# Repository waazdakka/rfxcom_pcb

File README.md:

# RFXCom PCB

This PCB aims to replace wires in a RFXCom project using:
* an Arduino Mega 2560
* a RXB6 Super Heterodyne receiver
* a XD-FST FS1000A emitter

(See https://opendomotech.com/fabriquer-rflink-alternative-diy-du-rfxcom/)

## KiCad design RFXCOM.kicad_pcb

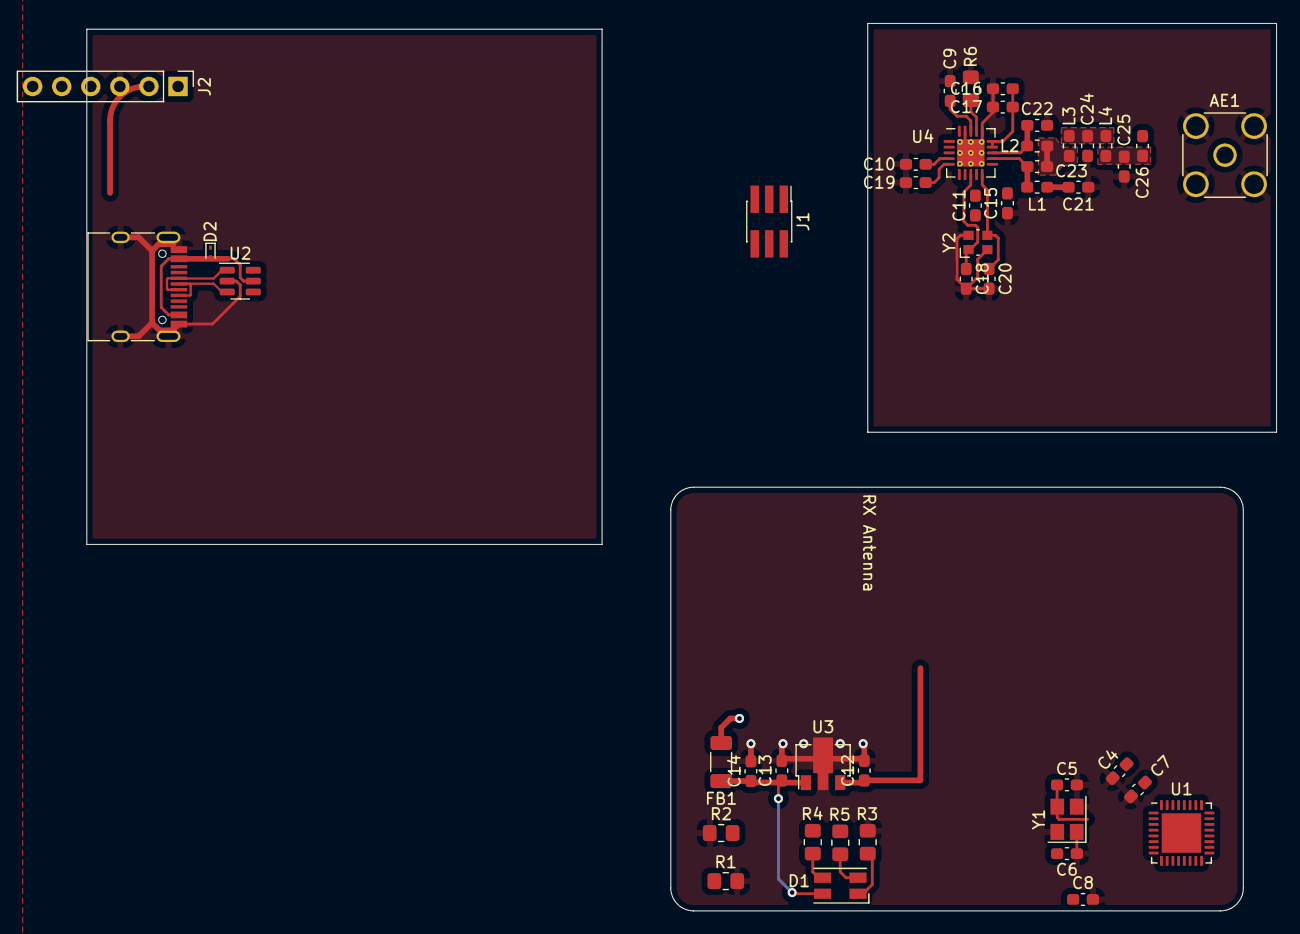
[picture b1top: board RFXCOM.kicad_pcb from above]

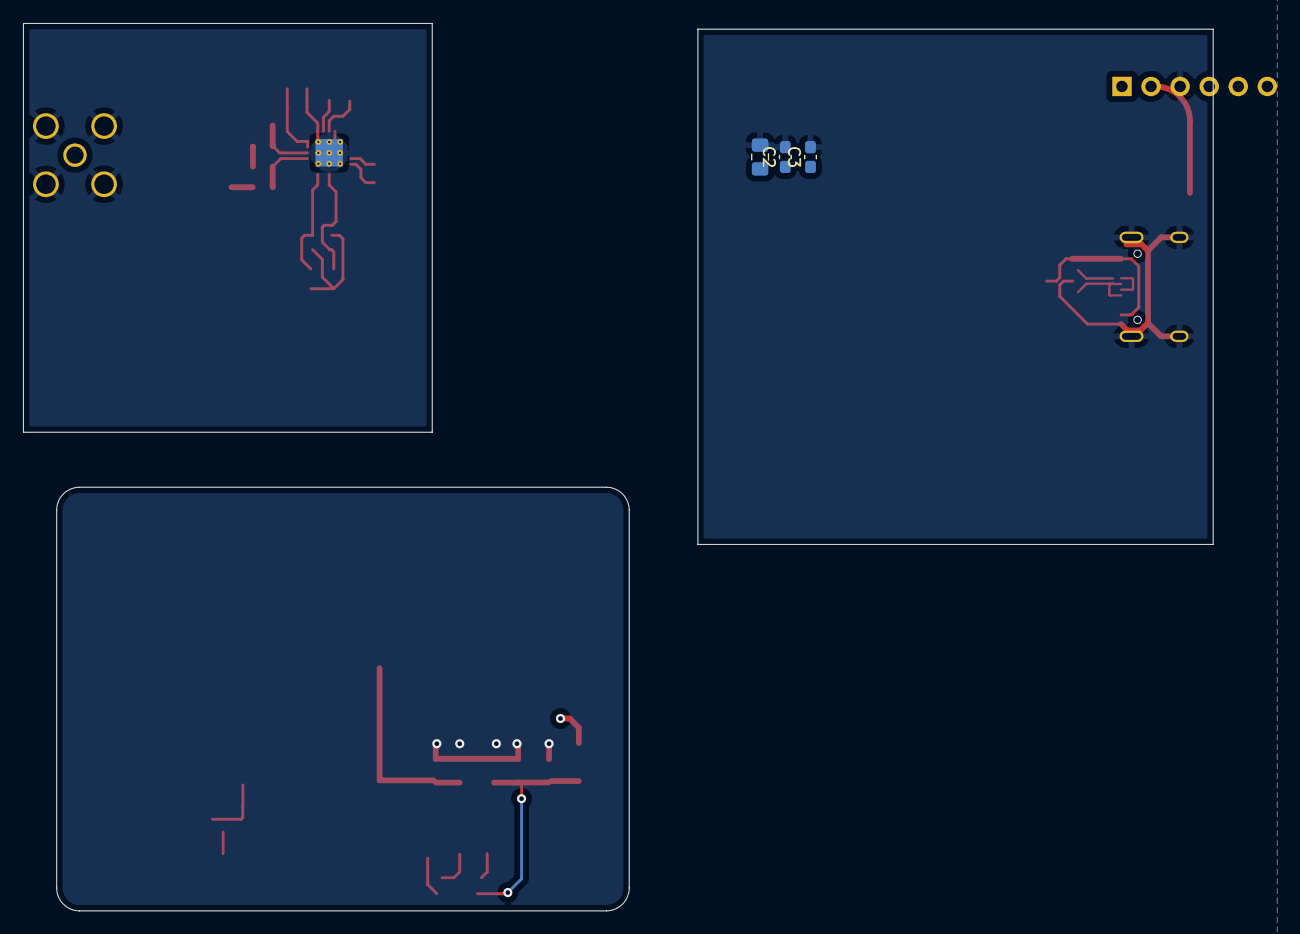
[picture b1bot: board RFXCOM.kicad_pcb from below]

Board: 2 copper layers, 103.9 x 77.5 mm, 49 parts (3 on the bottom side), 32 nets.

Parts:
AE1: Antenna_Shield; SMA_Amphenol_132134_Vertical
C1: 4u7; C_0805_2012Metric_Pad1.18x1.45mm_HandSolder
C2, C3, C7, C9, C10, C11, C15, C16, C17, C19: 100n; C_0603_1608Metric_Pad1.08x0.95mm_HandSolder
C4, C5: 10p; C_0603_1608Metric_Pad1.08x0.95mm_HandSolder
C6, C14: 1u; C_0603_1608Metric_Pad1.08x0.95mm_HandSolder
C8: 10n; C_0603_1608Metric_Pad1.08x0.95mm_HandSolder
C12: 2u; C_0603_1608Metric_Pad1.08x0.95mm_HandSolder
C13: 3u3; C_0603_1608Metric_Pad1.08x0.95mm_HandSolder
C18, C20: 22pF; C_0603_1608Metric_Pad1.08x0.95mm_HandSolder
C21: 220pF; C_0603_1608Metric_Pad1.08x0.95mm_HandSolder
C22, C23: 3.9pF; C_0603_1608Metric_Pad1.08x0.95mm_HandSolder
C24: 8.2pF; C_0603_1608Metric_Pad1.08x0.95mm_HandSolder
C25: 5.6pf; C_0603_1608Metric_Pad1.08x0.95mm_HandSolder
C26: 0.9pF; C_0603_1608Metric_Pad1.08x0.95mm_HandSolder
D1: LED_AGRB; LED_RGB_Wuerth-PLCC4_3.2x2.8mm_150141M173100
D2: ESD9X5.0ST5G; D_SOD-923
FB1: 120R; L_1206_3216Metric_Pad1.22x1.90mm_HandSolder
J1: SWD; PinHeader_2x03_P1.27mm_Vertical_SMD
J2: SWD_Connector; PinHeader_1x06_P2.54mm_Vertical
J6: USB_C_Receptacle_USB2.0; USB_C_Receptacle_HRO_TYPE-C-31-M-12
L1, L2, L4: 27nH; L_0603_1608Metric_Pad1.05x0.95mm_HandSolder
L3: 22nH; L_0603_1608Metric_Pad1.05x0.95mm_HandSolder
R1, R2: 5k1; R_0805_2012Metric_Pad1.20x1.40mm_HandSolder
R3: 130; R_0805_2012Metric_Pad1.20x1.40mm_HandSolder
R4, R5: 30; R_0805_2012Metric_Pad1.20x1.40mm_HandSolder
R6: 56k; R_0805_2012Metric_Pad1.20x1.40mm_HandSolder
U1: STM32L412KBTx; QFN-32-1EP_5x5mm_P0.5mm_EP3.45x3.45mm
U2: USBLC6-2SC6; SOT-23-6
U3: LD2981ABU33TR; SOT-89-3
U4: CC110L; Texas_S-PVQFN-N20_EP2.4x2.4mm_ThermalVias
Y1: 16M; Crystal_SMD_Abracon_ABM8G-4Pin_3.2x2.5mm
Y2: 26M; Crystal_SMD_Abracon_ABM10-4Pin_2.5x2.0mm

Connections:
+3.3V: C1.1, C2.1, C3.1, C9.2, C10.2, C11.2, C13.1, C14.1, C15.2, C16.2, C17.2, D1.1 (A), FB1.1, J1.1, U1.1 (VDD), U1.17 (VDD), U3.1 (VO), U4.4 (DVDD), U4.9 (AVDD), U4.11 (AVDD), U4.14 (AVDD), U4.15 (AVDD), U4.18 (DGUARD)
+3.3VA: C6.1, C8.1, FB1.2, U1.5 (VDDA)
+5V: C12.1, D2.2 (A2), J6.A4 (VBUS), J6.A9 (VBUS), J6.B4 (VBUS), J6.B9 (VBUS), U2.5 (VBUS), U3.3 (VI)
/MCU/SWCLK: J1.4, J2.2, U1.24 (PA14)
/MCU/SWDIO: J1.2, J2.4, U1.23 (PA13)
/MCU/SWO: J1.6, J2.6, U1.26 (PB3)
/MCU/USB_D+: U1.22 (PA12), U2.4 (I/O2)
/MCU/USB_D-: U1.21 (PA11), U2.6 (I/O1)
/MCU/~RST: C7.2, J1.3, J2.5, U1.4 (NRST)
/USB & Power Supply/USB_C_D+: J6.A6 (D+), J6.B6 (D+), U2.3 (I/O2)
/USB & Power Supply/USB_C_D-: J6.A7 (D-), J6.B7 (D-), U2.1 (I/O1)
GND: AE1.2 (Shield), C1.2, C2.2, C3.2, C4.1, C5.1, C6.2, C7.1, C8.2, C9.1, C10.1, C11.1, C12.2, C13.2, C14.2, C15.1, C16.1, C17.1, C18.2, C19.1, C20.2, C21.1, C22.2, C24.2, C25.2, D2.1 (A1), J1.5, J2.3, J6.A1 (GND), J6.A12 (GND), J6.B1 (GND), J6.B12 (GND), J6.S1 (SHIELD), R1.2, R2.1, R3.2, R6.2, U1.16 (VSS), U1.32 (VSS), U2.2 (GND), U3.2 (GND), U4.16 (GND), U4.19 (GND), U4.21 (PAD), Y1.2, Y1.4, Y2.2, Y2.4
unnamed: C4.2, U1.2 (PC14), Y1.3
unnamed: C5.2, U1.3 (PC15), Y1.1
unnamed: C19.2, U4.5 (DCOUPL)
unnamed: C21.2, L1.2
unnamed: C22.1, L2.2, U4.13 (RF_N)
unnamed: C23.1, L1.1, U4.12 (RF_P)
unnamed: C23.2, L2.1, L3.2
unnamed: C25.1, C26.1, L4.1
unnamed: AE1.1 (A), C26.2
unnamed: D1.2 (GK), R4.1
unnamed: D1.3 (RK), R3.1
unnamed: D1.4 (BK), R5.1
unnamed: J6.A5 (CC1), R1.1
unnamed: J6.B5 (CC2), R2.2
unnamed: C24.1, L3.1, L4.2
unnamed: R4.2, U1.29 (PB6)
unnamed: R5.2, U1.30 (PB7)
unnamed: R6.1, U4.17 (RBIAS)
unnamed: C18.1, U4.8 (XOSC_Q1), Y2.1
unnamed: C20.1, U4.10 (XOSC_Q2), Y2.3

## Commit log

2022-02-03 Add Kicad files
2022-02-03 Rework the schematics a bit with labels. Add a RXB6 footprint. Also add a .gitignore
2022-02-03 Remove local prl file
2022-10-14 New pcb on arduino mega pro, smoothed tracks, 2 antennas
2022-10-14 Fix labels on pcb, add screenshot
2022-10-14 Add readme
2022-11-07 Add XKFST component footprint
2022-11-11 Use correct footprint for TX
2022-11-11 stm32 based pcb
2022-11-28 add cc110L
